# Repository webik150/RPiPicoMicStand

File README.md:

# Rapic Micsta
-# Raspberry Pi Pico Microphone Stand

This project aims to create a motorized microphone stand using old NEMA-17 stepper motors from Prusa MK3, controllable through a LAN web server hosted on a RPi Pico W using MicroPython.

The software part operates in two modes:

- **Pairing Mode**: When no Wi-Fi credentials are available at startup, or wi-fi connection is unsuccessful, the device creates a Wi-Fi Access Point (AP) and serves as a captive portal to allow users to configure the Wi-Fi settings. It is also possible to control the stand in this way in case you need to record in the field without any wifi for whatever reason.
- **Work Mode**: Once Wi-Fi credentials are saved, the device connects to the saved network and serves a control website on the local network.

### Updates
- **2025-04-21**: Update PCB to V2.1. It uses a much simpler and cheaper design. It's now just 2 layers instead of 4 and should be compatible with more types of TMC2209.
- **2024-12-15**: Made a V2 of the PCB, it's much smaller, uses SMD components and TMC2209 instead of A4988. I also added a connector for an OLED display.
- **2024-11-02**: PCB was tested out to be working so I added files for it along with pics. Feel free to have it made, I usually use JLCPCB for that. I also added an 8SEG display to the thing last minute, which means there's no connector for it on the PCB, however you can just solder 4 pins to the top of the Pico like in the pic below.

## Features
- Movement on X and Y axes (Forward/Back and Left/Right)
- Mic rotation on one axis
- Optional 8SEG display for debugging, info, stuff.
- Powered by 12V, idk how many A will be needed yet.
- I'll try to make as much of the actual structure 3D printable
- The software side is just a HTML page that sends commands through AJAX rn.

## Requirements

- **Hardware**:
  - PCB V2
    - 1x Raspberry Pi Pico W (Pico W 1 is recommended for now as Pico W 2 micropython is in pre-release)
    - 3x TMC2209. I'm using black+green V2, others *should* work, but sometimes the pin layout differs.
    - 1x 12V 3A power supply
    - 5V Buck converter (most I've seen support different input voltages 5-30V). Should support 3A.
    - (optionally) SSD1306 OLED display. 128x64 works out of the box, 128x32 needs additional tweaks.
  - Stand itself
    - No idea yet.

- **Software**:
  - MicroPython installed on the Pico W
  - MicroPython modules:
    - `network` for Wi-Fi functionality
    - `socket` for HTTP server implementation
    - `ujson` for saving/loading Wi-Fi credentials

## Installation & Setup
idk if this is correct, ChatGPT came up with these instructions and I haven't had time to check them yet lol.

1. **Flash MicroPython on Raspberry Pi Pico W**:
    - Download the MicroPython firmware for Pico W from [here](https://micropython.org/download/rp2-pico-w/).
    - Flash the firmware to your Pico W using the Thonny IDE or another method.

2. **Clone the Repository**

3. **Upload Files to Pico W**:
    - Use Thonny or another IDE to upload the required Python files to your Pico W. The key files include:
        - `main.py`: The main logic for the pairing mode, Wi-Fi connection, and work mode.
        - `img/`: Folder containing images for the UI.
        - `index.html`: The control webpage.
        - `modules/`: Folder containing Python modules for the HTTP server and Wi-Fi configuration.

4. **Modify the Configuration**:
    - If you want to set a custom SSID and password for the access point, edit the following lines in `main.py`:

5. **Running the Project**:
    - Plug in the Raspberry Pi Pico W, and the script will automatically run.
    - If the device is unable to connect to a Wi-Fi network, it will enter **Pairing Mode**, where you can connect to the access point `RPi_Pico_Setup` and configure the network settings.
    - Once the Wi-Fi credentials are applied, the Pico W will switch to **Work Mode** and serve the control webpage on the local network.

## Usage

### Pairing

1. Connect to the Wi-Fi access point `RPiMicStand` with the password `12345678`.
2. Your device (phone or computer) should automatically open a captive portal page.
3. Select a network from the dropdown and enter the Wi-Fi password.
4. Press "Apply" to save the credentials and switch to work mode.

### Work Mode

1. The Pico W connects to the saved Wi-Fi network and launches a web server on port `80`.
2. Access the control page by navigating to the Pico's IP address in a web browser (use `wlan.ifconfig()` to find the IP).
3. Use the sliders, buttons, and other controls on the page to interact with the Pico's GPIO pins or perform other tasks.

## PCB
KiCAD files are in the `PCB` folder. It could definitely be made much smaller, I might make a v2 sometime just for the fuck of it, or if necessary. 

Right now RaPiPiMiSt uses 14 GPIO pins (3 for each motor, 5 for the display).

### Possible improvements (V2 Wishlist):
  * Use SMD components instead of THT. It's just resistors and capacitors so nothing fancy.
  * Get rid of the DIP switches and control the pins through Pico, there's enough PINS still.
    * Should this even be configurable? I could theoretically hardwire it so that X/Y motors use 1/2 step and Z motor uses 1/16 step.
    * If configurable, each motor would use 6 pins (23 total, which still fits). Alternatively only Z axis could be configurable.
  * Add a connector for the display directly on the board
  * Maybe switch over to an OLED display, which is cheaper, much more versatile and uses one less pin.
    * Downside is I have to learn to make an UI for that, but it sounds fun.
  * The power pin is made for a classic dupont pin rn, might be better to put it on the edge somewhere and make it use an actual on-board connector. Less wires.
  * I limited myself to 2 layer PCB, but 4 layer one isn't actually that much more expensive and could make stuff much smaller.
  * The A4988 is loud and has no stall detection. I could switch to a TMC2209 which is bit more expensive but would allow for automatic calibration and less pins used.
  * Idk what the fail rate of these drivers is but they could be soldered to the board instead of using a socket.
  * I could actually use vias instead of trying to go around everything lol.
  * The pico could be soldered directly to the board without any headers

RaPiPiMiSt PCB v01

Finished thing

## Pics

**Control website**:
TODO

**Stand**:
TODO

## License

This project is licensed under the MIT License. See the [LICENSE](LICENSE) file for details.

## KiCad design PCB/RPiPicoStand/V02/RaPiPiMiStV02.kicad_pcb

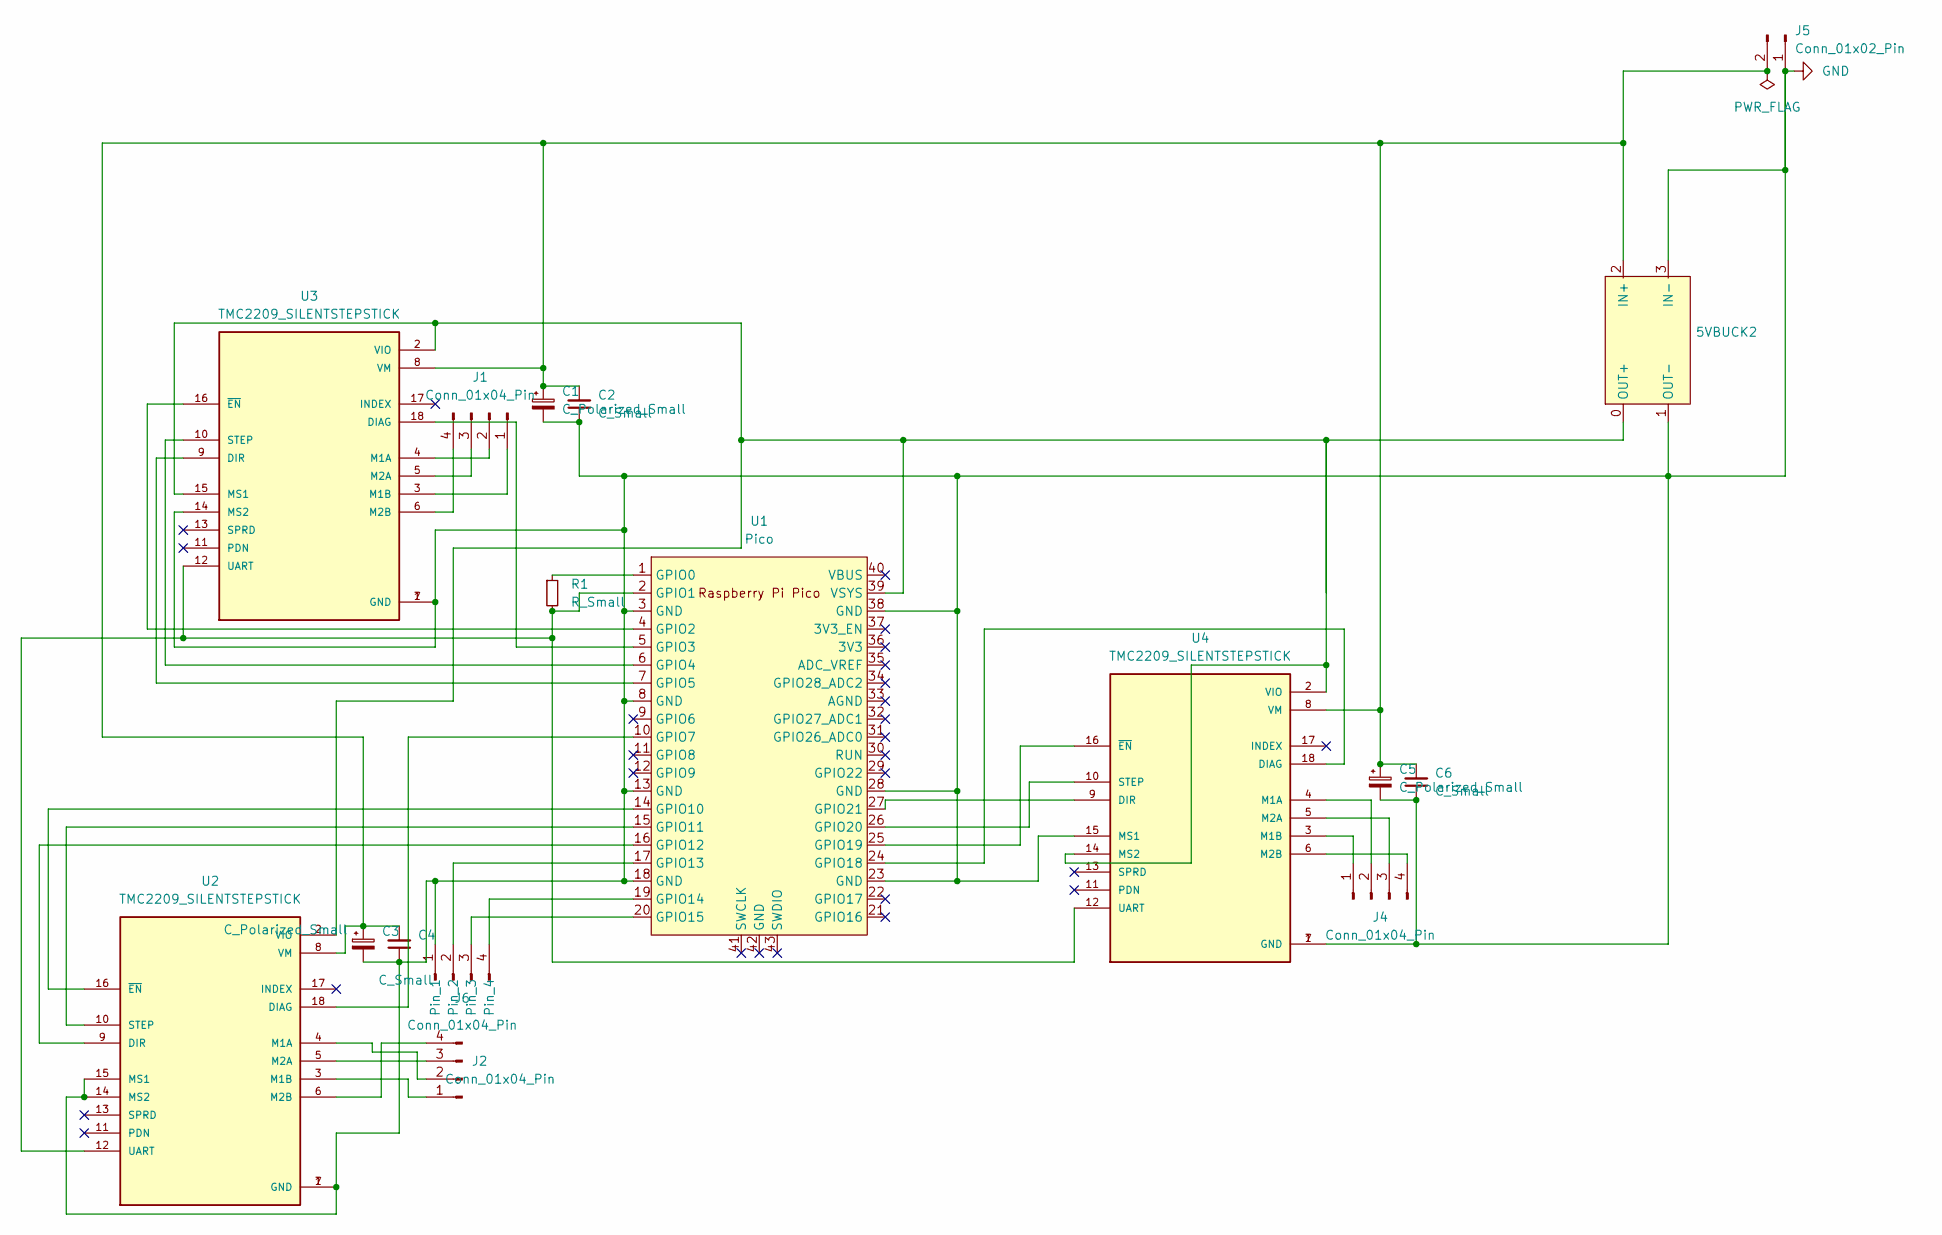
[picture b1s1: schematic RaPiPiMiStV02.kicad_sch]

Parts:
5VBUCK2: BUCK Converter 5-30V 5V 3A smd
C1, C3, C5: C_Polarized_Small; CP_Elec_6.3x7.7
C2, C4, C6: C_Small; C_0603_1608Metric
J1, J2, J4, J6: Conn_01x04_Pin; PinSocket_1x04_P2.54mm_Vertical
J5: Conn_01x02_Pin; PinHeader_1x02_P2.54mm_Vertical
R1: R_Small; R_0603_1608Metric_Pad0.98x0.95mm_HandSolder
U1: Pico; RPi_Pico_SMD_TH
U2, U3, U4: TMC2209_SILENTSTEPSTICK; MODULE_TMC2209_SILENTSTEPSTICK; PARTREV 1.20

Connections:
GND: 5VBUCK2.1 (OUT-), 5VBUCK2.3 (IN-), C1.2, C2.1, C3.2, C4.1, C5.2, C6.1, J5.1, J6.1, U1.3 (GND), U1.8 (GND), U1.13 (GND), U1.18 (GND), U1.23 (GND), U1.28 (GND), U1.38 (GND), U2.1 (GND), U2.7 (GND), U2.14 (MS2), U2.15 (MS1), U3.1 (GND), U3.7 (GND), U3.14 (MS2), U4.1 (GND), U4.7 (GND), U4.15 (MS1)
unnamed: 5VBUCK2.2 (IN+), C1.1, C2.2, C3.1, C4.2, C5.1, C6.2, J5.2, U2.8 (VM), U3.8 (VM), U4.8 (VM)
unnamed: 5VBUCK2.0 (OUT+), U1.39 (VSYS), U2.2 (VIO), U3.2 (VIO), U3.15 (MS1), U4.2 (VIO), U4.14 (MS2)
unnamed: J1.1, U3.3 (M1B)
unnamed: J1.2, U3.4 (M1A)
unnamed: J1.3, U3.5 (M2A)
unnamed: J1.4, U3.6 (M2B)
unnamed: J2.1, U2.3 (M1B)
unnamed: J2.2, U2.4 (M1A)
unnamed: J2.3, U2.5 (M2A)
unnamed: J2.4, U2.6 (M2B)
unnamed: J4.1, U4.3 (M1B)
unnamed: J4.2, U4.4 (M1A)
unnamed: J4.3, U4.5 (M2A)
unnamed: J4.4, U4.6 (M2B)
unnamed: J6.2, U1.17 (GPIO13)
unnamed: J6.3, U1.20 (GPIO15)
unnamed: J6.4, U1.19 (GPIO14)
unnamed: R1.1, U1.1 (GPIO0)
unnamed: R1.2, U1.2 (GPIO1), U2.12 (UART), U3.12 (UART), U4.12 (UART)
unnamed: U1.4 (GPIO2), U3.16 (~EN)
unnamed: U1.5 (GPIO3), U3.18 (DIAG)
unnamed: U1.6 (GPIO4), U3.10 (STEP)
unnamed: U1.7 (GPIO5), U3.9 (DIR)
unnamed: U1.10 (GPIO7), U2.18 (DIAG)
unnamed: U1.14 (GPIO10), U2.16 (~EN)
unnamed: U1.15 (GPIO11), U2.10 (STEP)
unnamed: U1.16 (GPIO12), U2.9 (DIR)
unnamed: U1.24 (GPIO18), U4.18 (DIAG)
unnamed: U1.25 (GPIO19), U4.16 (~EN)
unnamed: U1.26 (GPIO20), U4.10 (STEP)
unnamed: U1.27 (GPIO21), U4.9 (DIR)

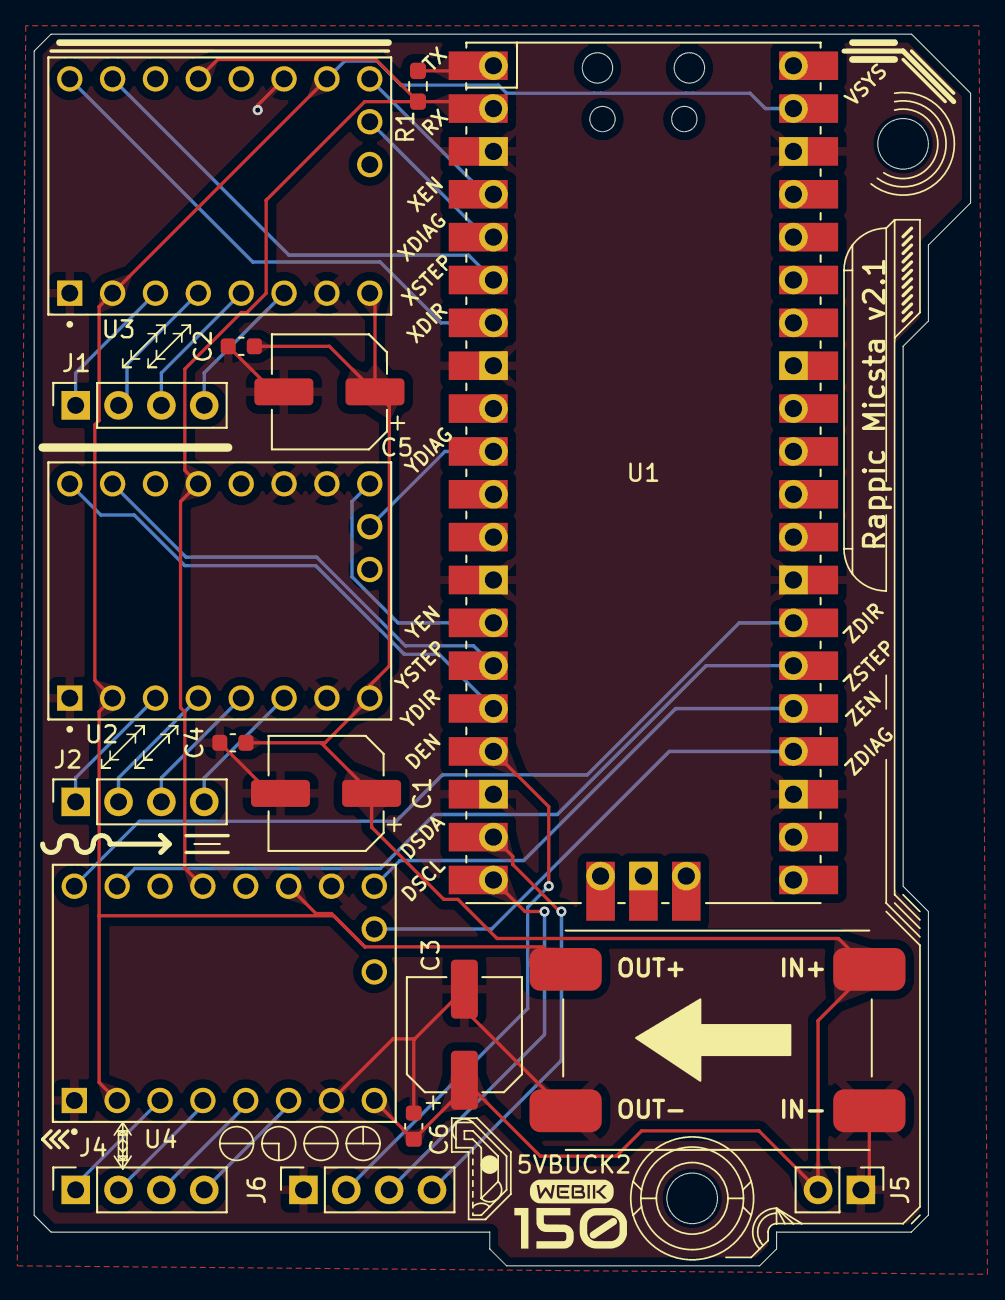
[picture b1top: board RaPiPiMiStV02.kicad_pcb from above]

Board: 2 copper layers, 55.5 x 73.0 mm, 17 parts (0 on the bottom side), 32 nets.

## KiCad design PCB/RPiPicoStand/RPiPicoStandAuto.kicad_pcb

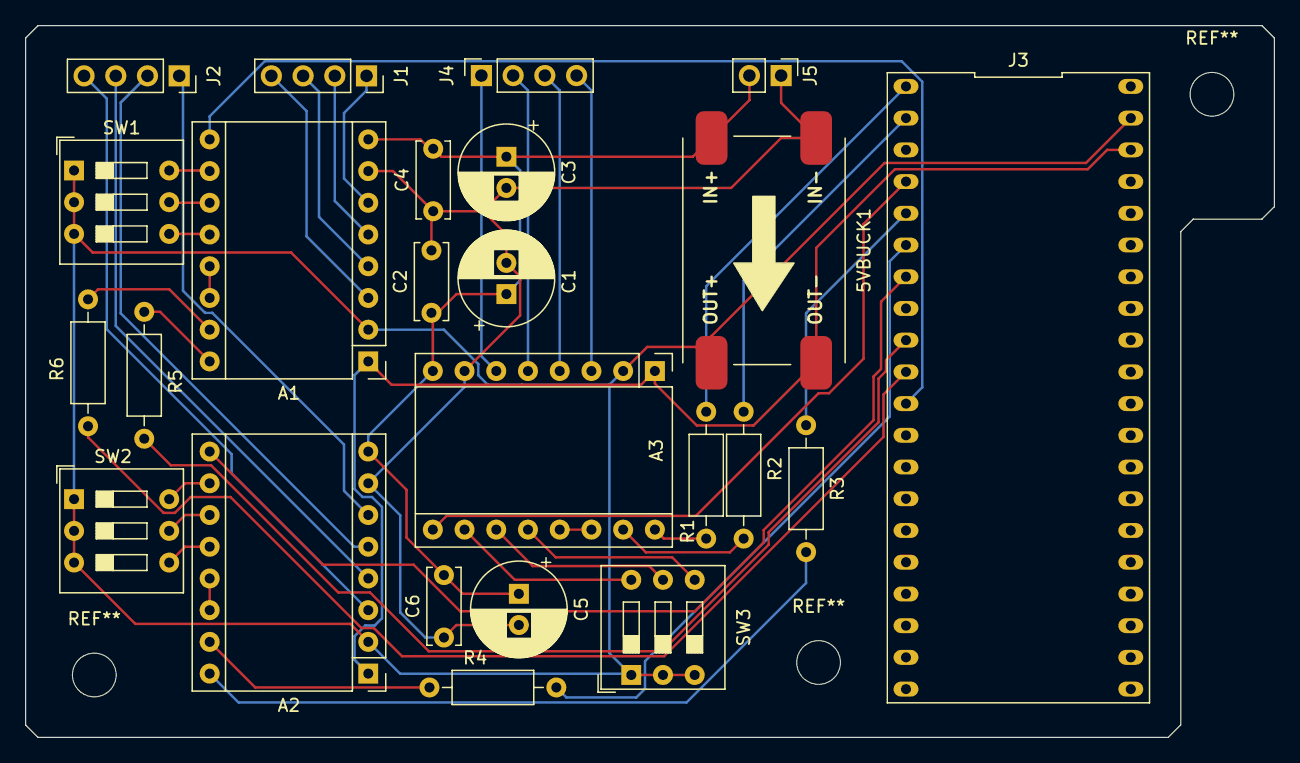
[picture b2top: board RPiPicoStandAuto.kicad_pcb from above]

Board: 2 copper layers, 100.0 x 57.0 mm, 24 parts (0 on the bottom side), 40 nets.

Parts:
5VBUCK1: BUCK Converter 5-30V 5V 3A smd
A1, A2, A3: Pololu_Breakout_A4988; Pololu_Breakout-16_15.2x20.3mm
C1, C3, C5: C_Polarized_Small; CP_Radial_D7.5mm_P2.50mm
C2, C4, C6: C_Small; C_Disc_D6.0mm_W2.5mm_P5.00mm
J1, J2, J4: Conn_01x04_Pin; PinSocket_1x04_P2.54mm_Vertical
J3: Conn_02x20_Counter_Clockwise; DIP-40_709_ELL socket W18Pins W21
J5: Conn_01x02_Pin; PinHeader_1x02_P2.54mm_Vertical
R1, R2, R3, R4, R5, R6: R_Small; R_Axial_DIN0207_L6.3mm_D2.5mm_P10.16mm_Horizontal
SW1, SW2, SW3: SW_DIP_x03; SW_DIP_SPSTx03_Slide_9.78x9.8mm_W7.62mm_P2.54mm

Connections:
5V: 5VBUCK1.0 (OUT+), A1.2 (VDD), A2.2 (VDD), A3.2 (VDD), J3.39, SW1.1, SW1.2, SW1.3, SW2.1, SW2.2, SW2.3, SW3.1, SW3.2, SW3.3
5VGND: 5VBUCK1.1 (OUT-), A1.1 (GND), A2.1 (GND), A3.1 (GND), J3.38
12V: 5VBUCK1.2 (IN+), A1.8 (VMOT), A2.8 (VMOT), A3.8 (VMOT), C1.1, C2.2, C3.1, C4.2, C5.1, C6.2, J5.2
12VGND: 5VBUCK1.3 (IN-), A1.7 (GND), A2.7 (GND), A3.7 (GND), C1.2, C2.1, C3.2, C4.1, C5.2, C6.1, J5.1
unnamed: A1.4 (1A), J1.3
unnamed: A1.3 (1B), J1.4
unnamed: A1.5 (2A), J1.2
unnamed: A1.6 (2B), J1.1
unnamed: A1.16 (DIR), R5.2
unnamed: A1.10 (MS1), SW1.6
unnamed: A1.11 (MS2), SW1.5
unnamed: A1.12 (MS3), SW1.4
unnamed: A1.15 (STEP), R6.1
unnamed: A1.9 (~ENABLE), J3.11
unnamed: A2.4 (1A), J2.3
unnamed: A2.3 (1B), J2.4
unnamed: A2.5 (2A), J2.2
unnamed: A2.6 (2B), J2.1
unnamed: A2.16 (DIR), R3.1
unnamed: A2.10 (MS1), SW2.6
unnamed: A2.11 (MS2), SW2.5
unnamed: A2.12 (MS3), SW2.4
unnamed: A2.15 (STEP), R4.1
unnamed: A2.9 (~ENABLE), J3.7
unnamed: A3.4 (1A), J4.3
unnamed: A3.3 (1B), J4.4
unnamed: A3.5 (2A), J4.2
unnamed: A3.6 (2B), J4.1
unnamed: A3.16 (DIR), R1.1
unnamed: A3.10 (MS1), SW3.6
unnamed: A3.11 (MS2), SW3.5
unnamed: A3.12 (MS3), SW3.4
unnamed: A3.15 (STEP), R2.1
unnamed: A3.9 (~ENABLE), J3.4
unnamed: J3.1, R1.2
unnamed: J3.2, R2.2
unnamed: J3.5, R3.2
unnamed: J3.6, R4.2
unnamed: J3.9, R5.1
unnamed: J3.10, R6.2

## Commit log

2024-09-09 init
2024-09-09 Create LICENSE
2024-09-30 add test code for turning the motors
2024-09-30 add controls for individual motors
2024-10-01 create Motor class create RPicoStand class create JSON class with static methods for serializing and deserializing config change /configure endpoint to allow for setting motor speeds change how confi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
2024-10-31 add pico 8-seg display support show status messages and device IP on wifi connection add static and rolling text support
2024-11-02 move display code to the main python file to decrease number of files needed to be flashed change motor pins to actually reflect the pins used by the PCB disable all motors on start
2024-11-02 update readme add some images
2024-11-05 add gitignore
2024-11-05 add the whole KiCAD project
2024-11-18 add super basic support for the SSD1306 OLED display
2024-11-20 add basic image reading and showing
2024-11-20 add V2 kicad project
2024-11-23 add icons and board bmp
2024-11-24 silkboard updates
2024-11-24 add teardrops, fix planes
2024-11-24 fix name of the pcb
2024-11-26 factory outputs
2024-11-29 change into 64h display
2025-03-31 Remove legacy frontend and backend code for RPi Pico Mic Stand
    Deleted unused `index.html` and `main.py` to clean up the repository. This removes obsolete web interface scripts, hardware control logic, and display effects to prepare for a streamlined implementat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
2025-03-31 fix uart connections on the PCB
2025-04-21 add some debugging code
2025-04-21 Update PCB design to V2.1 and adjust related files
    Updated the PCB to version 2.1, introducing a simpler and cheaper 2-layer design compatible with more TMC2209 types. Adjusted KiCad project settings, output directories, and port configurations to al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
2025-04-21 Update README hardware section with clarification details
    Added recommendations for Raspberry Pi Pico W versions and noted potential pin layout differences for TMC2209 variants. Adjusted power supply voltage for accuracy and provided further clarification f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
2025-04-21 Optimize motor initialization and error handling
    Refactored motor initialization to include better GSTAT error checks and conditional setup functions, improving robustness. Removed redundant initialization code and centralized logic in `RPicoStand`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
2025-05-08 Refactor and enhance motor control and display initialization.
    Improved motor handling with new stallguard threshold testing, updated microstepping configurations, and enhanced homing routines. Display initialization now includes detection handling and improved 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
